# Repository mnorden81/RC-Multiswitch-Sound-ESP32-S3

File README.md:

# RC-Multiswitch-Sound-ESP32-S3

RC-Multiswitch mit 8 Kanaelen plus Soundmodul auf einem ESP32-S3-DevKitC-1.

Frueher `CRSF-Multiswitch-Sound-ESP32-S3`, umbenannt passend zu RC-Multiswitch-ESP32-C3 und -S3.

Kombiniert den RC-Multiswitch mit einem Soundmodul auf einer Platine: 8 Schaltkanaele ueber TBD62083APG (Nachfolger des ULN2803A) und Soundausgabe ueber I2S, Sounds von microSD. Ziel ist ein Modul fuer Modelle, die Licht und Sound zusammen brauchen.

Ausfuehrliche Projektbeschreibung: [docs/Projektbeschreibung.docx](docs/Projektbeschreibung.docx)

## Projektvideo

Rund zwei Minuten Überblick über das ganze CRSF-Ökosystem: CRSF-Router, Multiswitch, Soundmodule, der ESP-NOW-CRSF-Link mit Funk in den Modulen und die Prüfstände für WebUI und Lua-Menü. Bild anklicken, dann startet das Video auf GitHub. Das Video liegt im Repo [RC-CRSF-Router-ESP32-S3](https://github.com/mnorden81/RC-CRSF-Router-ESP32-S3/tree/main/docs/video), weil es alle Module gemeinsam zeigt.

## Merkmale
- 8 Schaltkanaele ueber TBD62083APG, Kontroll-LED je Kanal
- UART A (Eingang), UART B und UART C als JST PH 4
- Audio: PCM5102A-DAC mit externem TPA3118-Verstaerker (HW-327, mono, aus VLOAD; Quelle mono: Kanal L direkt an den Verstaerker, kein Mono-Mix)
- microSD-Kartenmodul (6-polig) ueber SPI, Versorgung fest 3,3 V vom ESP32-Board (nur reine 3,3-V-Module verwenden)

## Hardware (v0.8, Entwurf, nur Schaltplan)
Board: ESP32-S3-DevKitC-1 N16R8 (oder Clone)

- Lastspannung 3S LiPo, 9-12,6 V (VLOAD) an CN2 (JST PH 2), TVS-Diode P6KE15A als Schutz.
- Treiber TBD62083APG (DMOS, Nachfolger des ULN2803A, gleiche Pinbelegung; ein ULN2803A passt weiterhin in den Sockel), 8 Kanaele, max. 500 mA je Kanal, Summe aller Kanaele ca. 1,5 A. Spannungsabfall am Ausgang nur ca. 0,2-0,4 V statt ca. 1 V beim ULN2803A.
- R9-R16 (THT 1/4 W) zwischen Treiber-Ausgang und Stiftleiste J1: Es ist kein Wert vorgegeben. Der Anwender muss die Widerstaende selbst passend zu Verbraucher und Lastspannung (3S, 9-12,6 V) auslegen, Strom und Verlustleistung beachten.
- R1-R8 und LED1-LED8 (3 mm) als Kontroll-LED je Kanal, vom Steuersignal Sn (3,3 V) gegen GND. Auch hier legt der Anwender die Werte selbst fest. Eine Empfehlung fuer die Kontroll-LEDs steht im Schaltplan.
- Keine Pulldowns und keine Widerstaende in den UART-Leitungen. Der ESP32 wird aus +5 V von CN1 (BEC/Empfaenger) versorgt.

### Belegung
| Funktion | GPIO |
|---|---|
| S0..S7 | IO4, IO5, IO6, IO7, IO15, IO16, IO1, IO2 |
| UART A (CN1, Eingang) | TX IO17, RX IO18 |
| UART B (J5) | TX IO39, RX IO40 |
| UART C (J6) | TX IO41, RX IO42 |
| SD (SPI) | CS IO10, MOSI IO11, SCK IO12, MISO IO13 |
| I2S | BCLK IO14, LRCK IO21, DOUT IO47 |

### Anschluesse
- CN1, J5, J6: UART A/B/C als JST PH 4 horizontal (S4B-PH-K)
- CN2 Last 3S LiPo (9-12,6 V) (JST PH 2), CN4 Lautsprecherausgang (JST PH 2, SPK+ / SPK-)
- J2 PCM5102A-Modul: Pin 1-6 = Stiftleiste (VIN, GND, LCK, DIN, BCK, SCK), Pin 7-10 = Ausgangspads G, R, G, L. Die Quelle ist mono: Pad L (Pin 10) und G (Pin 7, 9) gehen per Leiterbahn direkt an J11, Pad R (Pin 8) bleibt unbenutzt (No-Connect). Kein Mono-Mix, keine Mischwiderstaende.
- J11 TPA3118-Modul (HW-327), wird auf die Platine geloetet: Pad 1 IN, 2 GND, 3 PWR+ (VLOAD), 4 PWR- (GND), 5 OUT+ und 6 OUT- (zu CN4); die MUTE-Pads bleiben offen
- J9 microSD-Modul (6 Pins, VCC an 3V3 des ESP32-Boards, eigener Footprint mit Befestigungsloechern)

### Hinweise
- Gesperrte GPIOs: IO0/3/45/46 (Strapping), IO19/20 (USB), IO26-37 (Flash/PSRAM), IO43/44 (UART0). IO38/48 je nach Board an der RGB-LED.
- Footprint ESP32-S3-DevKitC-1_THT mit Reihenabstand 25,4 mm. Vor dem Layout am echten Board nachmessen. Eigene Footprints fuer PCM5102A, microSD-Modul und TPA3118-Modul liegen in hardware/footprints.pretty; die Masse sind aus Fotos geschaetzt und vor dem Layout nachzumessen.
- Nicht gleichzeitig USB und BEC anschliessen, ohne die Schutzdiode des Boards zu pruefen.

## Firmware (v1.12, nicht auf Hardware getestet)
Arduino-Sketch [firmware/RC_Multiswitch_Sound](firmware/RC_Multiswitch_Sound), Beschreibung in [firmware/README.md](firmware/README.md), alle Versionen in [CHANGELOG.md](CHANGELOG.md).

Reine Zusammenfuehrung von zwei bestehenden Firmwares:
- Schaltteil: RC-Multiswitch-ESP32-S3 v4.06 (= ESP32-Multiswitch-Basis V3/TXRX mit S3-Teilen): 8 Ausgaenge, Blinken, PWM, MWprop, bis 3 Konfigurationen je Ausgang, MKan-Gruppen, CRSF-Modulkette.
- Soundteil: ESP32-Sound-Basis_Ziege-One v7.21: Motor (start/loop/shut) und 24 Sounds von der SD-Karte, Upload der WAV-Dateien per WLAN.
- Gemeinsam: RC-System (CRSF oder SBUS auf UART A), WLAN und Web-UI, Lua-Menue am Sender, UART B/C (CRSF-Modulkette, S.Port, GPS, Raw), Firmware-Update per WLAN, Einstellungs-Backup im Flash und auf der SD-Karte.

Neu gegenueber den Basis-Firmwares (Entscheidungen 21.-28.10.2026):
- Zwei Adressen: Schalt-Adresse (Ausgaenge, zugleich CRSF-Geraeteadresse) und Sound-Adresse (Einzelkanal-Sounds). Gleiche Zahl = dieselben Schalter schalten beides.
- Status-LED in der Web-UI waehlbar: IO48 (DevKitC-1 v1.0, Vorgabe) oder IO38 (v1.1). Ab v1.08 dasselbe Farbschema wie alle Module: grün langsam = OK, rot schnell = Failsafe / kein RC-Link, rot Aufblitzen (kurz alle 1 s) = kein Signal, blau Doppelblitz = doppelte Moduladresse, violett statt grün/rot = WLAN an. Rot und Grün vertauscht? Lua Global > „LED Farbfolge“ umstellen (Vorgabe GRB).
- Lua-Menue: Ordner zeigen ihren aktuellen Wert (z. B. „Ausgang 1 (Kanal_L 5)“, „Einstellungen (ELRS CRSF)“), Felder ohne Wirkung werden ausgeblendet (z. B. reine SBUS-Felder, Blinkzeiten bei Dauerlicht). Das RC-System wird im Lua nur angezeigt, umstellen geht in der Web-UI. Reihenfolge im Hauptmenü: Version, Global, Ausgang 1–8, WLAN, UART B/C, Motor, Einstellungen, Gerätename, Sounds, Sound-Zuordnung, Funk.
- Klangqualität (ab v1.12): Mischer repariert. Ein Kanal wurde bei jedem negativen Sample zerstört, der eingebaute „Kompressor“ hat alles über ca. −9 dB verzerrt (jetzt ein sauberer Begrenzer, der nur bei Übersteuerung eingreift), Volumen über 100 % kippt nicht mehr über, andere Abtastraten und die Motor-Drehzahl werden weich umgerechnet (lineare Interpolation, kein Phasensprung an der Puffergrenze), 8-Bit-WAV wird richtig gelesen. Nicht auf Hardware getestet.
- Lua-Ordner „Ausgaenge“ (ab v1.11, wie Multiswitch v5.05): oben „Ausgang Nr“ (1–8) wählen, darunter die Einstellungen dieses Ausgangs. 71 statt 132 Lua-Felder.
- Lua-Ordner „Sounds“ (ab v1.10, gleich in allen Soundmodulen): oben „Sound Nr“ (1–24) wählen, darunter Name, Quelle, Kanal Nr, Volumen, Wiedergabe Mode und Test Sound dieses Sounds. Damit sind alle 24 Sounds am Sender einstellbar.
- Funk (ab v1.10, wie Multiswitch v5.04 und CRSF-Router): RC-System „CRSF + Funk senden (Zentrale)“ am Empfänger oder „CRSF aus Funk (Teilnehmer)“, dann bleibt UART A frei. Kennung und Funkkanal bei allen Modulen eines Fahrzeugs gleich einstellen (Reiter RC-System, Karte „Funk“, oder Lua-Ordner „Funk“). Reiter „Funk“ zeigt Verbindung, Verlust und RSSI. Der Access Point läuft dann auf dem Funkkanal.
- Eigener Name je Sound und je Ausgang (16 Zeichen), Vorgabe "Sound N" bzw. "Ausgang N".

## Firmware flashen

Es gibt drei Wege. Ein neues Modul wird einmal per USB geflasht (Weg 1 oder Weg 2), danach geht jedes Update bequem per WLAN (Weg 3).

| Weg | Braucht | Einstellungen im Modul |
|---|---|---|
| 1. Fertige Datei aus GitHub + Web-Flasher | nur Chrome oder Edge | werden **gelöscht** |
| 2. Arduino IDE | Arduino IDE 2.x | bleiben erhalten |
| 3. Update per WLAN | Handy oder PC mit WLAN | bleiben erhalten |

### Weg 1: Fertige Firmware aus GitHub (ohne Arduino IDE)

GitHub baut die Firmware bei jeder Änderung automatisch (Workflow „Firmware bauen“).

1. Auf GitHub angemeldet sein (sonst gibt es keinen Download-Knopf).
2. In diesem Repo oben auf **Actions** klicken, links den Workflow **Firmware bauen** wählen.
3. Den obersten Lauf mit grünem Haken öffnen (Branch `main`).
4. Ganz unten unter **Artifacts** **RC_Multiswitch_Sound-S3** herunterladen und die ZIP-Datei entpacken. Darin liegen u. a. `RC_Multiswitch_Sound.ino.merged.bin` (Komplett-Image für USB) und `RC_Multiswitch_Sound.ino.bin` (nur für Weg 3).
   Steht dort nichts (Artefakte werden nach 90 Tagen gelöscht): rechts oben **Run workflow** → **Run workflow** klicken, nach ca. 3 Minuten ist ein neuer Lauf fertig.
5. ESP32-S3-DevKitC-1 mit einem USB-**Datenkabel** an den PC stecken (Buchse „USB“ oder „UART“, beide gehen). Für die Buchse „UART“ braucht Windows evtl. den Treiber für den USB-Seriell-Chip (CP210x oder CH343).
6. In **Chrome** oder **Edge** die Seite https://espressif.github.io/esptool-js/ öffnen (Espressif-Web-Flasher, Firefox geht nicht).
7. **Connect** klicken und den COM-Port des Moduls wählen. Klappt das nicht: Baudrate oben auf `115200` stellen und das Modul mit der BOOT-Taste in den Flash-Modus bringen (siehe Weg 2, „Wenn das Hochladen nicht klappt“).
8. Unter **Flash Address** `0x0` eintragen, mit **Datei auswählen** die `.merged.bin` wählen, dann **Program** klicken.
9. Wenn unten „Leaving…“ steht, das USB-Kabel kurz abziehen und wieder einstecken. Fertig.

> **Achtung:** Das Komplett-Image überschreibt den ganzen Flash (4 MB). Alle Einstellungen und die Sicherungen im Flash (die Sounds und Sicherungen auf der SD-Karte bleiben) sind danach weg. Vorher in der Weboberfläche die Einstellungen als Datei sichern (Schaltteil: Karte **Konfiguration sichern/wiederherstellen** → „Als Datei exportieren“, Soundteil: Karte **Konfiguration sichern / wiederherstellen** → „Export“ oder „Auf SD sichern“) und hinterher dort wieder importieren. Wer die Einstellungen behalten will, nimmt Weg 2 oder 3.

### Weg 2: Arduino IDE

**Einmalig einrichten**

1. Arduino IDE 2.x installieren (https://www.arduino.cc/en/software).
2. **Datei → Einstellungen → Zusätzliche Boardverwalter-URLs**: `https://espressif.github.io/arduino-esp32/package_esp32_index.json` eintragen.
3. **Werkzeuge → Board → Boardverwalter**: „esp32“ suchen, **esp32 von Espressif Systems** in Version **3.0.7 (in GitHub getestet; 3.3.12 geht auch)** installieren.
4. **Werkzeuge → Bibliotheken verwalten**: **Bolder Flight Systems SBUS 8.1.4**, **TinyGPSPlus 1.0.3** suchen und in genau dieser Version installieren.
   Alles andere (z. B. `src/RC_Common/`) liegt schon im Sketch-Ordner.

**Flashen**

1. Repo herunterladen: oben auf GitHub **Code → Download ZIP**, entpacken (oder den vorhandenen Ordner nehmen).
2. In der Arduino IDE **Datei → Öffnen** und `firmware/RC_Multiswitch_Sound/RC_Multiswitch_Sound.ino` wählen.
3. Unter **Werkzeuge** einstellen:

   | Einstellung | Wert |
   |---|---|
   | Board | **ESP32S3 Dev Module** |
   | USB CDC On Boot | **Enabled** |
   | USB Mode | **USB-OTG (TinyUSB)** (ab v1.04, für die SD-Karte als USB-Laufwerk; mit „Hardware CDC and JTAG“ läuft alles außer dem Laufwerk) |
   | Upload Mode | **USB-OTG CDC (TinyUSB)** (beim Hochladen über die Buchse „USB“) |
   | Flash Size | 4MB (32Mb) |
   | Partition Scheme | **Minimal SPIFFS (1.9MB APP with OTA/128KB SPIFFS)** |
   | PSRAM | **Disabled** |
   | Erase All Flash Before Sketch Upload | **Disabled** (sonst sind die Einstellungen weg) |

4. ESP32-S3-DevKitC-1 mit einem USB-**Datenkabel** an der Buchse **USB** an den PC stecken (die Buchse „UART“ geht auch, braucht aber evtl. den Treiber für den USB-Seriell-Chip CP210x oder CH343). Dann unter **Werkzeuge → Port** den neuen COM-Port wählen. Hinweis: Läuft die Firmware ab v1.04 (TinyUSB), bekommt das Modul eine andere COM-Port-Nummer als im Flash-Modus. Nach dem Hochladen also ggf. den Port neu wählen.
5. Auf den Pfeil **Hochladen** klicken. Am Ende steht „Hard resetting via RTS pin…“.
6. Das Modul startet von selbst neu. Wenn nicht: USB-Kabel kurz abziehen und wieder einstecken.

**Wenn das Hochladen nicht klappt** („Failed to connect“ oder „No serial data received“): Taste **BOOT** gedrückt halten, kurz **RST** drücken, BOOT loslassen. Das Board ist jetzt im Flash-Modus. Noch einmal **Hochladen**, danach einmal **RST** drücken.

### Weg 3: Update per WLAN (OTA)

1. Die Datei `RC_Multiswitch_Sound.ino.bin` besorgen: aus GitHub (Weg 1, Schritte 1–4) oder in der Arduino IDE mit **Sketch → Kompilierte Binärdatei exportieren** (liegt dann im Sketch-Ordner unter `build/`). Nicht die `.merged.bin` nehmen.
2. WLAN des Moduls einschalten: BOOT-Taste 2 s halten (oder Lua „WLAN jetzt“ bzw. automatisch ohne RC-Signal). Name **MultiSwitch**, Passwort `123456789` (falls nicht geändert).
3. Mit Handy oder PC in dieses WLAN gehen und im Browser http://192.168.1.1 öffnen.
4. Reiter **WiFi**, Karte **Firmware-Update (OTA)**: die `.bin`-Datei auswählen und hochladen. Das Modul startet danach neu, die Einstellungen bleiben erhalten.

Schlägt das Update fehl, läuft die alte Firmware einfach weiter. Das Modul beim Update am besten über den Empfänger/BEC versorgen, nicht nur über einen schwachen USB-Anschluss.

## Sound-Dateien und Zuordnung (ab v1.07)
Hochgeladene WAV-Dateien behalten ihren Namen. Umlaute werden ersetzt (ä → ae), Leerzeichen werden zu `_`, erlaubt sind A-Z, a-z, 0-9, `_` und `-`, höchstens 40 Zeichen plus `.wav`. Welche Datei auf welchem Platz spielt (Loop, Standgas, Start, Sound 1-24), speichert das Modul selbst. Dieselbe Datei darf auf mehreren Plätzen liegen.

- **Web-UI, Tab "Speicher"**: Speicherbelegung, je Platz eine Auswahlliste mit allen Dateien auf der SD-Karte, Liste der Dateien mit "spielt auf ...", Löschen und Hochladen mehrerer Dateien. Änderungen wirken sofort.
- **Lua, Ordner "Sound-Zuordnung"**: Platz wählen, dann bei "Datei" eine der gespeicherten Dateien (lange Namen gekürzt, höchstens 20 Dateien in der Liste).
- Alte SD-Karten laufen weiter: ohne gespeicherte Zuordnung gelten die festen Namen `loop.wav`, `shut.wav`, `start.wav`, `sound1.wav` ... `sound24.wav`.
- Die Zuordnung steht auch in der exportierten Konfiguration (`sound_files`).

## Ordner
- `hardware/`: KiCad-Projekt (Schaltplan, PCB, PDF, eigene Footprints, fp-lib-table). Entwurfsnotizen in [hardware/README-hardware.md](hardware/README-hardware.md).
- `firmware/`: Firmware (Arduino-Sketch `RC_Multiswitch_Sound`), Build in GitHub Actions.
- `hardware/gehaeuse/`: 3D-Druck-Gehaeuse (STL, STEP, CadQuery-Quelle), siehe [hardware/gehaeuse/README.md](hardware/gehaeuse/README.md).
  - Zwei Versionen: J1 als stehende Stiftleiste (Kabel nach vorne/oben) oder als gewinkelte Stiftleiste 2x8, deren Stecker vorne durch die Wand kommen. 3D-Vorschau mit bestueckter Platine: `hardware/gehaeuse/Gehaeuse3D_Vorschau.html` und `hardware/gehaeuse/Gehaeuse3D_Vorschau_gewinkelt.html`.
- `docs/`: Projektbeschreibung als DOCX.

## Stand
- Hardware: Schaltplan v0.8, PCB in Arbeit. ERC-Stand v0.3 (hardware/ERC.rpt): 1 Fehler (IO8 unbeschaltet, seit v0.4 mit No-Connect-Flag, plus Rest-Leitungsstueck entfernt) und 55 Warnungen (Bibliotheksversionen "power"/"Device"/"local", harmlos). Nach v0.8 ERC neu ausfuehren.
- Firmware: v1.09, baut in GitHub Actions, auf Hardware noch nicht getestet. Änderungen siehe [CHANGELOG.md](CHANGELOG.md).

## Offene Punkte
- R1-R16 vom Anwender je LED bzw. Verbraucher auslegen (3S, ca. 11-12 V); Helligkeit schwankt mit dem Ladezustand.
- Schaltplan v0.8 im PCB per F8 (Aktualisieren aus Schaltplan) uebernehmen: J10, R18, R19, J3, J4, R17, J7, J8 entfallen (Footprints ohne Symbol loeschen lassen), J2, J9 und J11 bekommen die neuen Modul-Footprints (J11 jetzt TPA3118 mit 6 Pads), CN3 entfaellt, CN4 (Lautsprecher) ist neu. hardware/*.pdf ist noch der Stand v0.1.
- ERC mit v0.8 neu ausfuehren; Symbolbibliothek "local" einbinden (reduziert die Warnungen).
- TPA3118-Modul (HW-327): Modul-Mindestspannung 8 V beachten (3S-Akku nicht unter ca. 9 V entladen, Abschaltung ueber Fahrregler/Unterspannungswaechter), MUTE-Header offen, Leiterbahnbreite und Stromaufnahme gegen CN2/CN4 (JST PH, ca. 2 A je Kontakt) pruefen.
- microSD-Modul muss ein reines 3,3-V-Modul sein (Standard-Module mit Spannungsregler bekommen sonst zu wenig Spannung); Pinreihenfolge am Modul gegen J9 (VCC, CS, MOSI, SCK, MISO, GND) pruefen.
- Module nachmessen und Footprints anpassen: PCM5102A, microSD-Modul, TPA3118 (Padlage, Befestigungsloecher, Belegung IN/GND per Multimeter pruefen), ESP32-S3-DevKitC-1.
- PCB-Layout erstellen
- Gehaeuse (hardware/gehaeuse/) am echten Aufbau pruefen: Hoehe Elko C1 (22 mm angenommen), ESP 13 mm ueber der Platine, Lage USB-C und microSD-Slot
- Firmware auf der Platine testen (Ausgaenge, Sound, SD-Karte, Status-LED IO48/IO38)

## Sound-Aufbereitung (im Browser)

[Sound-Aufbereitung öffnen](https://raw.githack.com/mnorden81/RC-Multiswitch-Sound-ESP32-S3/main/werkzeuge/sound-aufbereitung.html#pcm) – prüft Audiodateien (WAV, MP3, M4A …) und wandelt sie passend für dieses Modul um: Multiswitch-Sound S3 (SD-Karte, PCM5102A). Ohne Installation, auch am Handy; nichts wird hochgeladen, alles läuft im Browser. Die Dateien behalten ihren Namen (Umlaute und Leerzeichen werden wie im Modul ersetzt), die Zuordnung zum Sound-Platz geschieht im Modul im Tab „Speicher“. Oben lässt sich das Modul umstellen. Selbst erzeugte, rechtefreie Testsounds (Hupe, Blinker, Rückfahrwarner, Martinshorn, Motor-Leerlauf als Schleife, Sweep 40 Hz–16 kHz) gibt es per Knopf „Testsounds einfügen“ oder direkt in [`werkzeuge/testsounds/`](werkzeuge/testsounds/).

## Prüfstand (WebUI und Lua im Browser)

In [`pruefstand/`](pruefstand/) liegt eine Seite, die die echte Weboberfläche und das Lua-Menü dieser Firmware im Browser zeigt (alle Varianten, Modul simuliert): [Prüfstand öffnen](https://raw.githack.com/mnorden81/RC-Multiswitch-Sound-ESP32-S3/main/pruefstand/pruefstand.html). Sie wird bei jeder Firmware-Änderung neu gebaut, die GitHub-Prüfung „Prüfstand" achtet darauf.

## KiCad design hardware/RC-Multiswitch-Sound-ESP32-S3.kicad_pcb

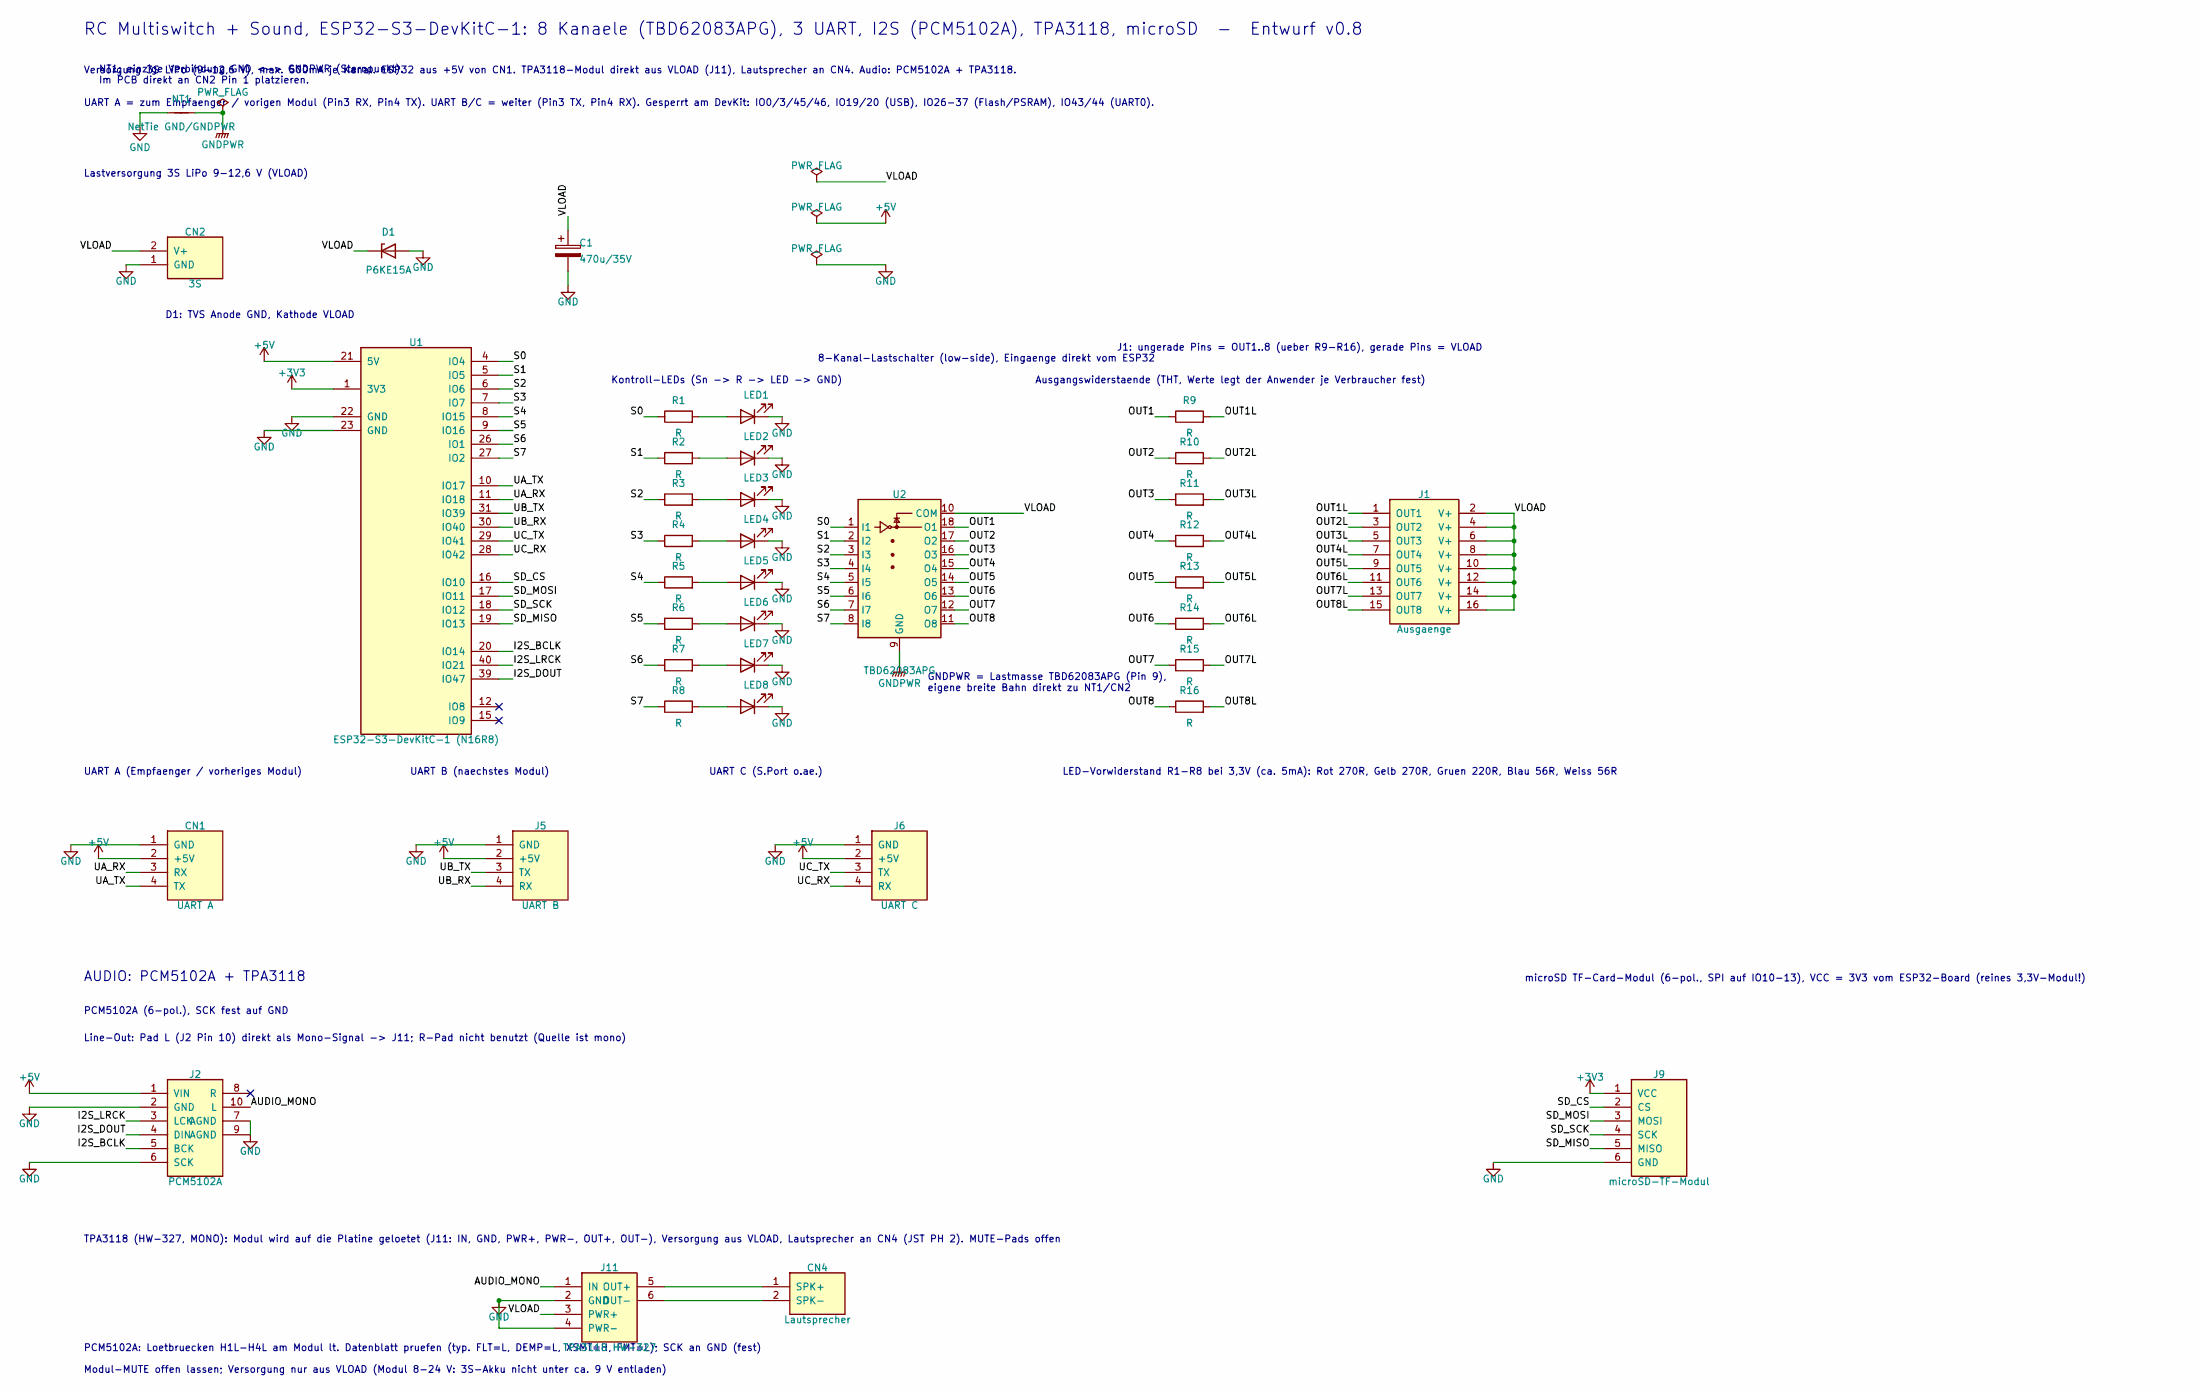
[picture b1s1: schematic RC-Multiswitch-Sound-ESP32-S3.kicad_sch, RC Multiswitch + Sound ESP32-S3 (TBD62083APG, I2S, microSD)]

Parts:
C1: 470u/35V; CP_Radial_D10.0mm_P5.00mm
CN1: UART A; JST_PH_S4B-PH-K_1x04_P2.00mm_Horizontal
CN2: 3S; JST_PH_S2B-PH-K_1x02_P2.00mm_Horizontal
CN4: Lautsprecher; JST_PH_S2B-PH-K_1x02_P2.00mm_Horizontal
D1: P6KE15A; D_DO-15_P12.70mm_Horizontal
J1: Ausgaenge; PinHeader_2x08_P2.54mm_Vertical
J2: PCM5102A; Mod_PCM5102A_GY_THT
J5: UART B; JST_PH_S4B-PH-K_1x04_P2.00mm_Horizontal
J6: UART C; JST_PH_S4B-PH-K_1x04_P2.00mm_Horizontal
J9: microSD-TF-Modul; Mod_microSD_SPI_THT
J11: TPA3118 HW-327; Mod_TPA3118_HW327_THT
LED1, LED2, LED3, LED4, LED5, LED6, LED7, LED8: LED; LED_D3.0mm
NT1: NetTie GND/GNDPWR; NetTie-2_SMD_Pad2.0mm
R1, R2, R3, R4, R5, R6, R7, R8, R9, R10, R11, R12, R13, R14, R15, R16: R; R_Axial_DIN0207_L6.3mm_D2.5mm_P7.62mm_Horizontal
U1: ESP32-S3-DevKitC-1 (N16R8); ESP32-S3-DevKitC-1_THT
U2: TBD62083APG; DIP-18_W7.62mm_Socket

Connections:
+3V3: J9.1 (VCC), U1.1 (3V3)
+5V: CN1.2 (+5V), J2.1 (VIN), J5.2 (+5V), J6.2 (+5V), U1.21 (5V)
/AUDIO_MONO: J2.10 (L), J11.1 (IN)
/I2S_BCLK: J2.5 (BCK), U1.20 (IO14)
/I2S_DOUT: J2.4 (DIN), U1.39 (IO47)
/I2S_LRCK: J2.3 (LCK), U1.40 (IO21)
/OUT1: R9.1, U2.18 (O1)
/OUT1L: J1.1 (OUT1), R9.2
/OUT2: R10.1, U2.17 (O2)
/OUT2L: J1.3 (OUT2), R10.2
/OUT3: R11.1, U2.16 (O3)
/OUT3L: J1.5 (OUT3), R11.2
/OUT4: R12.1, U2.15 (O4)
/OUT4L: J1.7 (OUT4), R12.2
/OUT5: R13.1, U2.14 (O5)
/OUT5L: J1.9 (OUT5), R13.2
/OUT6: R14.1, U2.13 (O6)
/OUT6L: J1.11 (OUT6), R14.2
/OUT7: R15.1, U2.12 (O7)
/OUT7L: J1.13 (OUT7), R15.2
/OUT8: R16.1, U2.11 (O8)
/OUT8L: J1.15 (OUT8), R16.2
/S0: R1.1, U1.4 (IO4), U2.1 (I1)
/S1: R2.1, U1.5 (IO5), U2.2 (I2)
/S2: R3.1, U1.6 (IO6), U2.3 (I3)
/S3: R4.1, U1.7 (IO7), U2.4 (I4)
/S4: R5.1, U1.8 (IO15), U2.5 (I5)
/S5: R6.1, U1.9 (IO16), U2.6 (I6)
/S6: R7.1, U1.26 (IO1), U2.7 (I7)
/S7: R8.1, U1.27 (IO2), U2.8 (I8)
/SD_CS: J9.2 (CS), U1.16 (IO10)
/SD_MISO: J9.5 (MISO), U1.19 (IO13)
/SD_MOSI: J9.3 (MOSI), U1.17 (IO11)
/SD_SCK: J9.4 (SCK), U1.18 (IO12)
/UA_RX: CN1.3 (RX), U1.11 (IO18)
/UA_TX: CN1.4 (TX), U1.10 (IO17)
/UB_RX: J5.4 (RX), U1.30 (IO40)
/UB_TX: J5.3 (TX), U1.31 (IO39)
/UC_RX: J6.4 (RX), U1.28 (IO42)
/UC_TX: J6.3 (TX), U1.29 (IO41)
/VLOAD: C1.1, CN2.2 (V+), D1.1 (K), J1.2 (V+), J1.4 (V+), J1.6 (V+), J1.8 (V+), J1.10 (V+), J1.12 (V+), J1.14 (V+), J1.16 (V+), J11.3 (PWR+), U2.10 (COM)
GND: C1.2, CN1.1 (GND), CN2.1 (GND), D1.2 (A), J2.2 (GND), J2.6 (SCK), J2.7 (AGND), J2.9 (AGND), J5.1 (GND), J6.1 (GND), J9.6 (GND), J11.2 (GND), J11.4 (PWR-), LED1.1 (K), LED2.1 (K), LED3.1 (K), LED4.1 (K), LED5.1 (K), LED6.1 (K), LED7.1 (K), LED8.1 (K), NT1.1, U1.22 (GND), U1.23 (GND)
GNDPWR: NT1.2, U2.9 (GND)
unnamed: CN4.1 (SPK+), J11.5 (OUT+)
unnamed: CN4.2 (SPK-), J11.6 (OUT-)
unnamed: LED1.2 (A), R1.2
unnamed: LED2.2 (A), R2.2
unnamed: LED3.2 (A), R3.2
unnamed: LED4.2 (A), R4.2
unnamed: LED5.2 (A), R5.2
unnamed: LED6.2 (A), R6.2
unnamed: LED7.2 (A), R7.2
unnamed: LED8.2 (A), R8.2

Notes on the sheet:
D1: TVS Anode GND, Kathode VLOAD
Versorgung 3S LiPo (9-12,6 V), max. 500mA je Kanal. ESP32 aus +5V von CN1. TPA3118-Modul direkt aus VLOAD (J11), Lautsprecher an CN4. Audio: PCM5102A + TPA3118.
AUDIO: PCM5102A + TPA3118
Ausgangswiderstaende (THT, Werte legt der Anwender je Verbraucher fest)
LED-Vorwiderstand R1-R8 bei 3,3V (ca. 5mA): Rot 270R, Gelb 270R, Gruen 220R, Blau 56R, Weiss 56R
PCM5102A: Loetbruecken H1L-H4L am Modul lt. Datenblatt pruefen (typ. FLT=L, DEMP=L, XSMT=H, FMT=L); SCK an GND (fest)
J1: ungerade Pins = OUT1..8 (ueber R9-R16), gerade Pins = VLOAD
Line-Out: Pad L (J2 Pin 10) direkt als Mono-Signal -> J11; R-Pad nicht benutzt (Quelle ist mono)
RC Multiswitch + Sound, ESP32-S3-DevKitC-1: 8 Kanaele (TBD62083APG), 3 UART, I2S (PCM5102A), TPA3118, microSD - Entwurf v0.8
microSD TF-Card-Modul (6-pol., SPI auf IO10-13), VCC = 3V3 vom ESP32-Board (reines 3,3V-Modul!)
PCM5102A (6-pol.), SCK fest auf GND
UART A (Empfaenger / vorheriges Modul)
Modul-MUTE offen lassen; Versorgung nur aus VLOAD (Modul 8-24 V: 3S-Akku nicht unter ca. 9 V entladen)
Lastversorgung 3S LiPo 9-12,6 V (VLOAD)
UART C (S.Port o.ae.)
Kontroll-LEDs (Sn -> R -> LED -> GND)
UART A = zum Empfaenger / vorigen Modul (Pin3 RX, Pin4 TX). UART B/C = weiter (Pin3 TX, Pin4 RX). Gesperrt am DevKit: IO0/3/45/46, IO19/20 (USB), IO26-37 (Flash/PSRAM), IO43/44 (UART0).
UART B (naechstes Modul)
TPA3118 (HW-327, MONO): Modul wird auf die Platine geloetet (J11: IN, GND, PWR+, PWR-, OUT+, OUT-), Versorgung aus VLOAD, Lautsprecher an CN4 (JST PH 2). MUTE-Pads offen
8-Kanal-Lastschalter (low-side), Eingaenge direkt vom ESP32
NT1: einzige Verbindung GND <-> GNDPWR (Sternpunkt). Im PCB direkt an CN2 Pin 1 platzieren.
GNDPWR = Lastmasse TBD62083APG (Pin 9), eigene breite Bahn direkt zu NT1/CN2

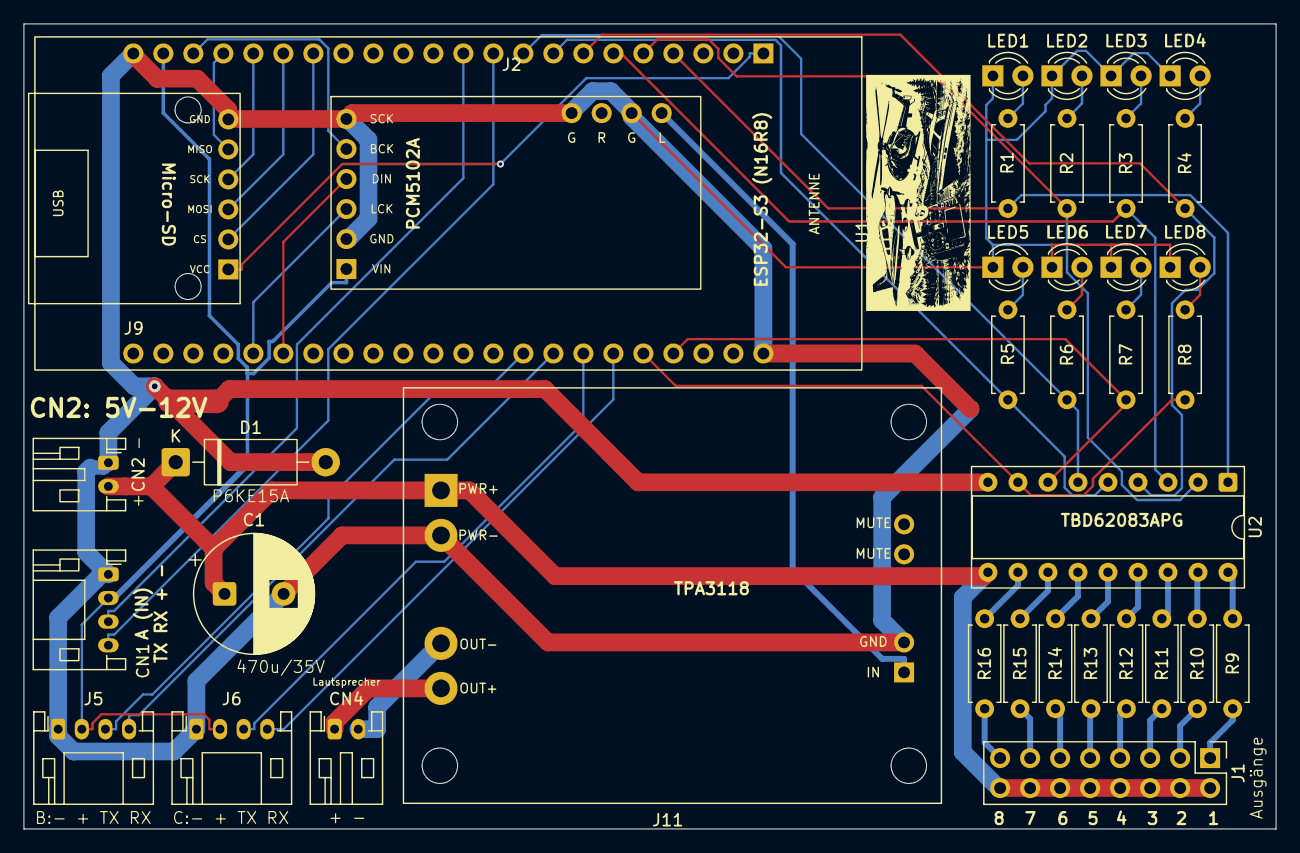
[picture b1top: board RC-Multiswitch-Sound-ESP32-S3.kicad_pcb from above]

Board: 2 copper layers, 106.0 x 68.2 mm, 38 parts (0 on the bottom side), 53 nets.

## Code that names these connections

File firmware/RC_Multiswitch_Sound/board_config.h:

/*
 * board_config.h  -  Pin- und Board-Konfiguration RC-Multiswitch-Sound v1.00
 *
 * Platine RC-Multiswitch-Sound-ESP32-S3 v0.9 mit ESP32-S3-DevKitC-1 N16R8
 * (oder Clone). Pinbelegung laut README.md (Abschnitt "Belegung") und
 * hardware/RC-Multiswitch-Sound-ESP32-S3.kicad_sch.
 *
 * Arduino-IDE-Einstellungen:
 *   Board:            ESP32S3 Dev Module
 *   USB CDC On Boot:  Enabled  (Debug-Ausgaben ueber USB, UART0 = UART A)
 *   Partition Scheme: Minimal SPIFFS (1.9MB APP with OTA/128KB SPIFFS)
 *                     (OTA-Update per WLAN + Einstellungs-Backup im Flash)
 *   PSRAM:            Disabled (wird nicht gebraucht)
 */
#pragma once
#include <Arduino.h>

#if !defined(CONFIG_IDF_TARGET_ESP32S3)
  #error "Bitte Board 'ESP32S3 Dev Module' waehlen"
#endif

#if !ARDUINO_USB_CDC_ON_BOOT
  #error "Bitte 'USB CDC On Boot: Enabled' einstellen - UART0 wird fuer UART A (CRSF/SBUS) gebraucht"
#endif

#define BOARD_S3
#define BOARD_NAME "S3 Kombi"

// Ausgaenge S0..S7 (Kanal 1..8), alle mit LEDC-Kanal
static constexpr uint8_t OutPin[8] = {4, 5, 6, 7, 15, 16, 1, 2};
static constexpr bool    OutPwm[8] = {true, true, true, true, true, true, true, true};

// UART A (CN1, Eingang vom Empfaenger) = UART0, CRSF oder SBUS
#define UART_A_SERIAL Serial0
static constexpr uint8_t UART_A_RX = 18;
static constexpr uint8_t UART_A_TX = 17;
// UART B (J5) = UART1
#define UART_B_SERIAL Serial1
static constexpr uint8_t UART_B_RX = 40;
static constexpr uint8_t UART_B_TX = 39;
// UART C (J6) = UART2
#define UART_C_SERIAL Serial2
static constexpr uint8_t UART_C_RX = 42;
static constexpr uint8_t UART_C_TX = 41;

// microSD (J9) ueber SPI
static constexpr uint8_t SD_CS   = 10;
static constexpr uint8_t SD_MOSI = 11;
static constexpr uint8_t SD_SCK  = 12;
static constexpr uint8_t SD_MISO = 13;

// I2S zum PCM5102A (J2), mono: der Verstaerker haengt am Kanal L
static constexpr uint8_t I2S_BCLK = 14;
static constexpr uint8_t I2S_LRC  = 21;
static constexpr uint8_t I2S_DOUT = 47;

static constexpr uint8_t BOOT_BTN_PIN = 0;

// RGB-LED (WS2812) des DevKitC-1: v1.0 an IO48, v1.1 an IO38. Der Pin wird
// in der Web-UI gewaehlt (NVS "ledpin", wirkt nach einem Neustart).
static constexpr int STATUS_LED_PIN_DEFAULT = 48;
static constexpr int STATUS_LED_PIN_ALT     = 38;
#define STATUS_LED_WS2812 1
static constexpr uint8_t STATUS_LED_BRIGHTNESS = 40;  // von 255, ca. 15 %
